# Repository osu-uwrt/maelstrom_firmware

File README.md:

# maelstrom_firmware

This repository holds the code for the embedded systems and other tools running on Maelstrom. There are two primary parts to this: the acoustics code, and the the coprocessor code/console. A brief overview of each of the systems is below. For detailed install instructions, see the acoustics and [copro](/Copro/README.md) README files. For more information about the hardware of these devices, see github.com/osu-uwrt/uwrt_electronics

## Coprocessor
The coprocessor has several primary tasks:

- read sensor values
- control thrusters
- communicate with the main computer

It does this with an onboard microcontroller, an STM32F405RGT6. This microcontroller board is loosely based on the pyboard from the micropython project. As such, the microcontroller is programmed using micropython. It is programmed using a USB connection, and talks with the main computer over the local network via websocket. Additionally, there is an operator console web app that shows current status of the coprocessor and allows the device to be controlled without having to open up the vehicle.

## Acoustics
The acoustics system is designed to be able to determine the direction and distance of an acoustic ping (between 20kHz - 40kHz frequency). This is used to navigate towards a pinger in the robot. Thus, the device has a lot of signal processing and alignment code

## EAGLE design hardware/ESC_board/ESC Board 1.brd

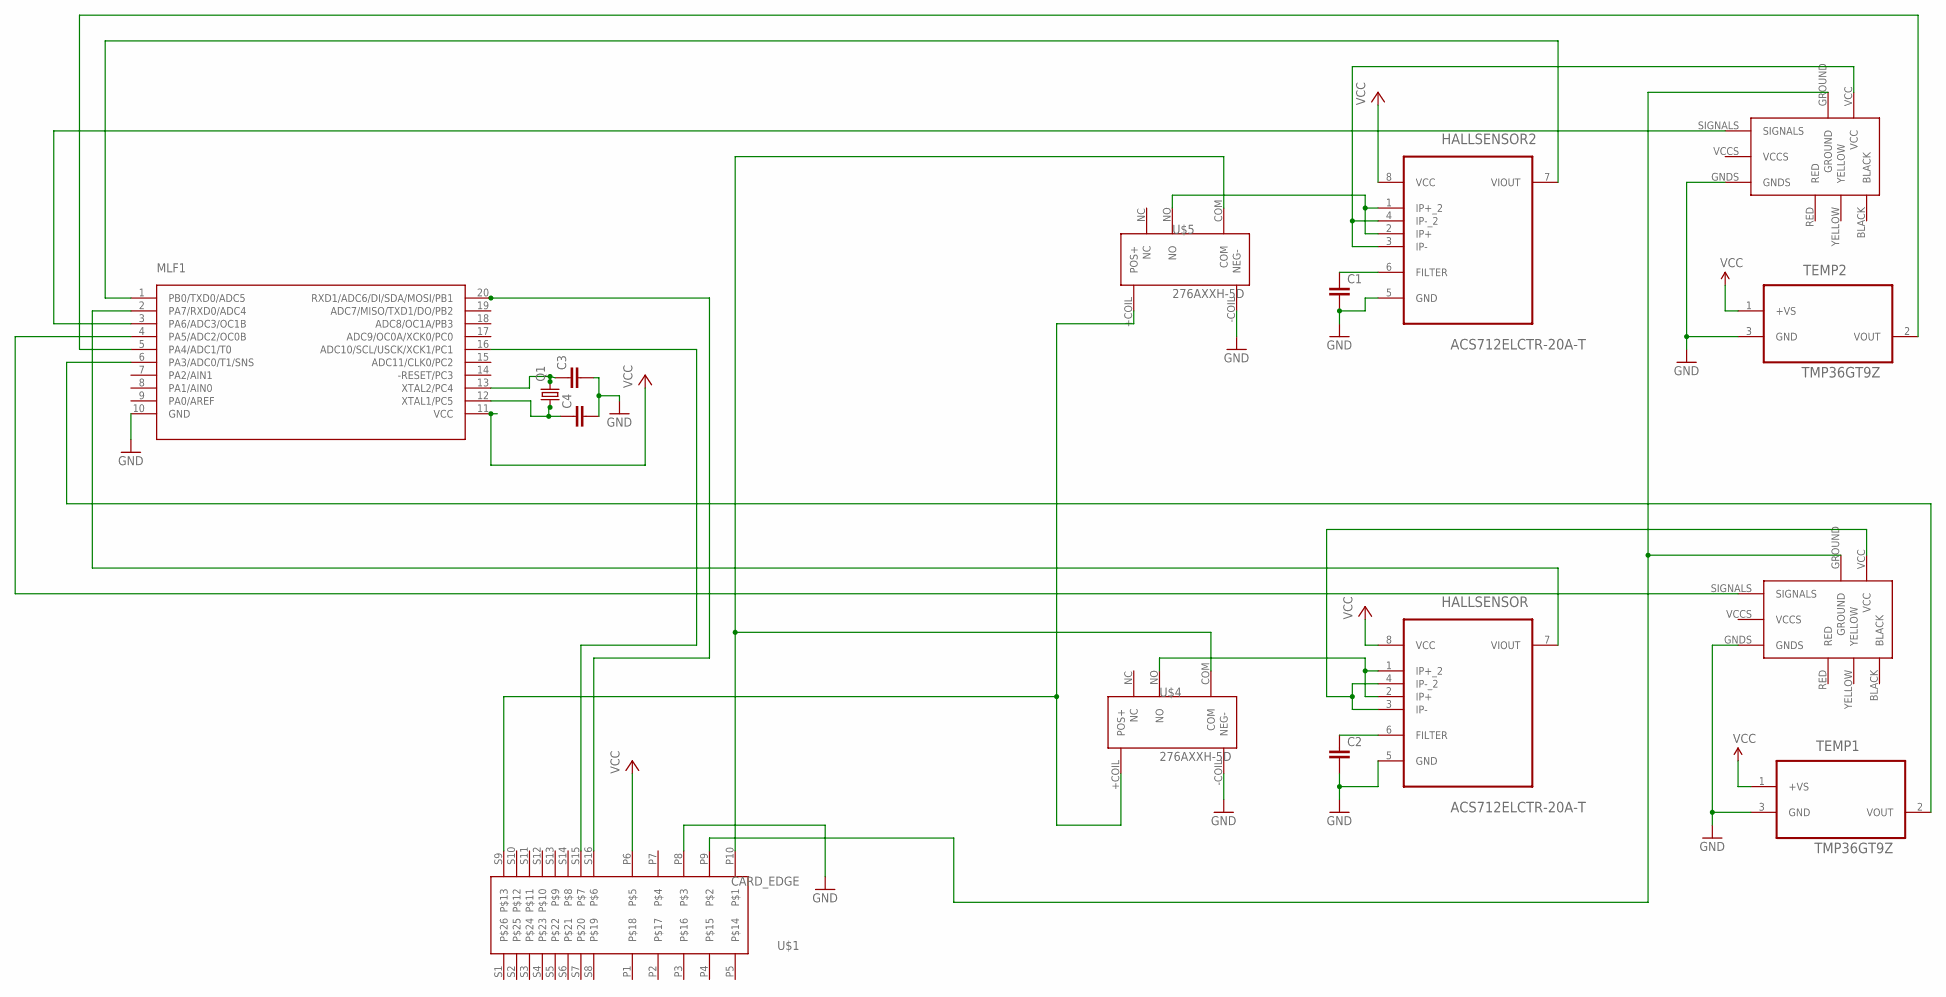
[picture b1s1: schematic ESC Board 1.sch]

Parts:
C1, C2, C3, C4: CAPEZ; CAP-PTH-SMALLEZ
HALLSENSOR, HALLSENSOR2: ACS712ELCTR-20A-T; SOIC127P600X175-8N
MLF1: ATTINY1634SOIC20; SOIC20
Q1: CRYTALTC26V; TC26V
TEMP1, TEMP2: TMP36GT9Z; TO127P254X533-3P
U$1: CARD_EDGE; EDGE_CONNECTOR
U$2, U$3: ESC30A; 30AESC
U$4, U$5: 276AXXH-5D

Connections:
BAT-: U$1.P9, U$2.GROUND, U$3.GROUND
GND: C1.2, C2.2, C3.2, C4.2, HALLSENSOR.5 (GND), HALLSENSOR2.5 (GND), MLF1.10 (GND), TEMP1.3 (GND), TEMP2.3 (GND), U$1.P8, U$2.GNDS, U$3.GNDS, U$4.-COIL (NEG-), U$5.-COIL (NEG-)
unnamed: MLF1.5 (PA4/ADC1/T0), TEMP2.2 (VOUT)
unnamed: MLF1.6 (PA3/ADC0/T1/SNS), TEMP1.2 (VOUT)
unnamed: MLF1.20 (RXD1/ADC6/DI/SDA/MOSI/PB1), U$1.S16
unnamed: MLF1.16 (ADC10/SCL/USCK/XCK1/PC1), U$1.S15
unnamed: HALLSENSOR2.7 (VIOUT), MLF1.1 (PB0/TXD0/ADC5)
unnamed: HALLSENSOR.7 (VIOUT), MLF1.2 (PA7/RXD0/ADC4)
unnamed: C3.1, MLF1.13 (XTAL2/PC4), Q1.2
unnamed: C4.1, MLF1.12 (XTAL1/PC5), Q1.1
unnamed: C1.1, HALLSENSOR2.6 (FILTER)
unnamed: HALLSENSOR2.3 (IP-), HALLSENSOR2.4 (IP-_2), U$3.VCC
unnamed: U$1.P10, U$4.COM, U$5.COM
unnamed: HALLSENSOR.3 (IP-), HALLSENSOR.4 (IP-_2), U$2.VCC
unnamed: MLF1.4 (PA5/ADC2/OC0B), U$2.SIGNALS
unnamed: MLF1.3 (PA6/ADC3/OC1B), U$3.SIGNALS
unnamed: C2.1, HALLSENSOR.6 (FILTER)
unnamed: HALLSENSOR.1 (IP+_2), HALLSENSOR.2 (IP+), U$4.NO
unnamed: HALLSENSOR2.1 (IP+_2), HALLSENSOR2.2 (IP+), U$5.NO
unnamed: U$1.S9, U$4.+COIL (POS+), U$5.+COIL (POS+)
VCC: HALLSENSOR.8 (VCC), HALLSENSOR2.8 (VCC), MLF1.11 (VCC), TEMP1.1 (+VS), TEMP2.1 (+VS), U$1.P6

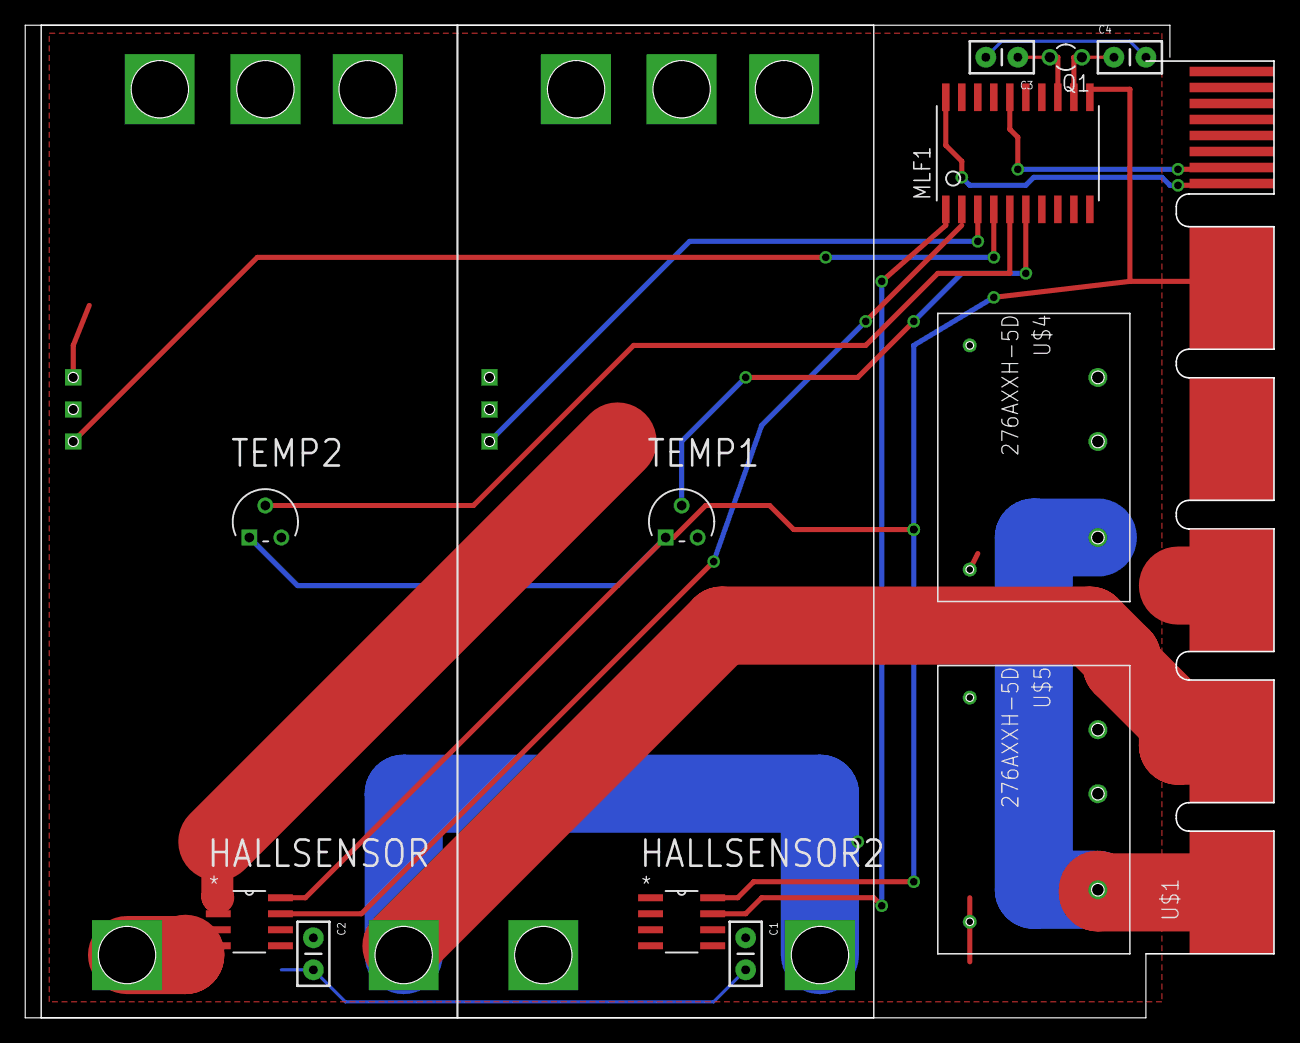
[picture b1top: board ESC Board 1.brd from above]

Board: 2 copper layers, 99.0 x 78.6 mm, 15 parts (0 on the bottom side), 21 nets.

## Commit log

2016-06-17 Move serial to hardware.
2016-06-17 Rename ATmega source files.
2016-06-17 Rewrite thruster controller.
2016-06-18 Add TWI library for ESC microcontrollers.
2016-06-18 Add ESC board firmware.
2016-06-18 Correct thruster controller firmware.
2016-06-20 Bit shift TWI data.
2016-06-22 Monitor power distribution board.
2016-06-26 Monitor battery output.
2016-06-29 It's giving me... attitude.
2016-06-30 internal oscillator calibration values, offset initial clock values
2016-06-30 rebased with iconor/master
2016-06-30 Update firmware timing and calibrate current sensors.
2016-07-01 Update power monitor rate.
2016-07-02 depth sensor
2016-07-02 Succesfully reads depth.
2016-07-02 Repair thruster controller sketch.
2016-09-07 added eagle files
2016-09-18 added up to date firmware
2016-10-24 total redesign is way better
2016-10-24 Update directory/file names.
2017-08-10 Putting old stuff into /old
2017-08-10 Initial commit of the firmware for the Co-Pro board
2017-08-11 Adding in coPro and powerSupply boards, might be moved later
2017-09-06 Cleaning up Hardware and Firmware, function prototype for LED
2017-09-06 Attempting to use the HAL API to handle all of our pin needs
2017-09-06 Adding Arduino Code and splitting to STM32 code
2017-09-07 Adding initial depth sensor firmware waiting for Benji to confirm
2017-09-08 Testing HAL initialization of stuff along with dabbling in ideas to split the team code out of the src
2017-09-08 Adding the README file
2017-09-10 Adding Team threads for Arduino replacement
2017-09-11 Adding Arduino/C based ros_lib to STM32
2017-09-11 Updated the Makefile to build
2017-10-06 Changed pins on arduino code for 10/7 pool test
2017-10-07 This should fix it, but who knows
2017-11-12 Initial commit of the rev 1 copro pin map
2018-01-25 Working commit of sanity
2018-02-12 Ordinary cleanup of our sins
2018-02-12 Initial commit of a Bibyk Abstraction layer by altering STM code less
2018-02-12 Adding stmComms, test suite with riptideSTM and computer communications
2018-02-12 Removed .idea and .DS_Store files, added .gitignore
2018-02-15 added queue example code
2018-02-15 add serial template for f405 (using FS)
2018-02-18 added new project, need to test
2018-02-18 Updating gitignore to ignore build files and cmake stuffs
2018-02-18 Updating the riptideSTM, abstraction works theoretically
2018-02-18 Yikes git is hard
2018-02-18 fixed the bugs
2018-02-19 Updating the switch messages for the copro rev1
2018-03-01 initial project commit
2018-03-01 working serial code for pool test - old board
2018-03-01 check message length implemented
2018-03-01 finished kill switch
2018-03-02 i2c is working, still need to format the message
2018-03-03 code complete; need to test
2018-03-04 revisions from pool test
2018-03-22 Just for Gus
2018-03-23 working with copro v3
2018-03-23 Revert "Merge branch 'march_pool_test' into new_changes"
    This reverts commit bc184a939472e353ee53c2bbd46ac80ecc62abe6, reversing
    changes made to 817e7272e0bf183608458219f8eef7cdb89f3fc0.
2018-03-23 Revert "working with copro v3"
    This reverts commit 817e7272e0bf183608458219f8eef7cdb89f3fc0.
2018-03-23 add folder and ioc - base start point
2018-03-23 Restored to working v3
2018-03-23 good depth sensor, need to test
2018-03-23 refactored ioc and cleaned up a bit
2018-03-25 Cleanup attempt 1
2018-03-25 Cleanup attempt 2
2018-03-25 Cleanup attempt
2018-03-25 working pool test code + unfinished i2c
2018-04-13 working april pool test - fixed depth sensor ftostring function
2018-05-16 Deleting old stuff out of repo
2018-05-16 Initial commit of mirkwood
2018-05-16 Updating Makefile to compile
2018-05-16 Going back to our roots, working but no status board
2018-05-16 Cleanup of old RTOS stuffs
2018-05-16 Migrating back to Atom building now
2018-05-16 Actually starting everything working temp
2018-05-16 Fixing print to display, temperature accurate
2018-05-16 Starting PWM timers, this is important
2018-05-17 Adding call for hardfault handler, working 517
2018-05-18 Adding current calculations for the battery balancer
2018-05-22 Fixing header file names
2018-05-28 Updating the .gitirnore
2018-05-28 Tyring to ignore the build files
2018-05-28 Adding the startup function to status board
2018-05-28 Global thermonuclear war of master
2018-05-28 Cleaning up the mirkwood branch
2018-05-28 Readme now reflects what we know
2018-05-31 Added acoustics
2018-06-06 Adding electro status message
2018-06-06 Merging the mirkwood branch with master
2018-06-22 latest FPGA
2018-06-22 Update gitignore
2018-06-27 Updating README and STM32 folder to reflect current code
2018-06-27 Adding the pneumatics arduino code
2018-06-27 Changing vehicle name
2018-09-21 New acoustics configuration with ddr3
2018-10-29 Commenting acoustics code
2018-10-29 Fixing errors
2018-11-16 Trying to fix broken fpga
2018-11-18 Fixed acoustics. Works with new board
2019-02-18 Addition of new copro stuff
2019-02-18 Updating gitignore
2019-02-18 Gitignore fix
2019-02-18 Python 3 compatibility
2019-02-18 More compatible
2019-02-19 Works on python 3
2019-02-20 Python 2 compatibility
2019-02-21 Adding polling example and allowing multiple commands to come through at once
2019-02-21 Comments
2019-02-21 python 2/3 support
2019-03-16 Adding hal
2019-03-16 website changes
2019-03-17 Updating httpproxy for copro
2019-03-17 Making the code work
2019-03-17 Implementing thruster off and temp
2019-03-17 Cleaning out website
2019-03-17 Fixing vulnerabilities
2019-03-18 Implementing temp and power graph plus copro code
2019-03-19 Error handling, leds, and pwm
2019-03-19 Added depth code
2019-03-20 Now able to get current state of copro
2019-03-21 Fixing control lines and adding status light code
2019-03-21 Fixed electricity plot and added switches command
2019-03-22 Depth works
2019-03-22 Quick fix
2019-03-23 Making it run on pc
2019-03-24 Cleaning up repo
2019-03-25 current stuff
2019-03-25 Cleanup and branding
2019-03-26 Fixed some issues with copro
2019-03-27 Works on all python 3
2019-03-27 depth card component
2019-03-27 Small changes
2019-04-02 enable closing of sockets
2019-04-02 Forgot to commit this
2019-04-21 added/fixed thruster current collection
2019-04-21 create command tester tool and update hal simulator
2019-04-21 Update main README
2019-04-21 Create copro docs
2019-04-21 add copro config files
2019-04-27 changed mobopower and thrusterpower to 12V and 5V
2019-04-27 New depth
2019-04-29 Better simulator
2019-05-01 Fixing some issues
2019-05-17 Added reset button and fixed copro bugs
2019-05-30 Reset switch
2019-06-06 Killswitch time and readme update
2019-06-06 Fixing depth sensor
2019-06-06 Ensure that time will work even on the wrap over
2019-06-08 Improved comms
2019-06-08 Fixing memory
2019-06-08 5V reset functionality on copro
2019-06-08 5V reset on copro
2019-06-11 Updating httpProxy
2019-07-15 thruster default on
2019-07-16 Thusters default on, after batteries are plugged in they will wait for one to dip below 18.5V and then disable the thrusters
2019-07-20 Initial commit of actuator firmware (arduino)
2019-07-24 Debugging
2019-07-24 Adding actuator board functionality
2019-07-24 Basics of actuator communication
2019-07-26 Last changes
2019-09-15 memory leak fix
2019-09-15 Fixed halSimulated and fixed memory fix
2019-09-15 fixed hal simulated
2019-09-19 Updated simulator and command tester
2019-09-22 Fix the variable unsable warning
2019-09-22 Added error checking to each thread
2019-09-22 I create a auto cooling funciton.
2019-10-12 I add function to see memory usage
2019-10-12 Just make it look neatly
2019-10-13 Command tester fix
2019-10-13 FIx some bugs and make sure everything is fine
2019-10-13 Fix memory monitor bug, add temp control funciton
2019-10-13 Added memory to operator console
2019-10-13 Remove TODO and modify the parameter of battery
2019-10-13 Added latency and thermostate to operator console
2020-01-30 Bump tinymce from 4.5.7 to 4.9.7 in /Copro/operator_console/website
    Bumps [tinymce](https://github.com/tinymce/tinymce-dist) from 4.5.7 to 4.9.7.
    - [Release notes](https://github.com/tinymce/tinymce-dist/releases)
    - [Changelog](https://github.com/tinymce/tinymce-dist/blob/4.9.7/changelog.txt)
    - [Commits](https://github.com/tinymce/tinymce-dist/compare/4.5.7...4.9.7)
2020-05-11 Bump tinymce from 4.5.7 to 4.9.10 in /Copro/operator_console/website
    Bumps [tinymce](https://github.com/tinymce/tinymce-dist) from 4.5.7 to 4.9.10.
    - [Release notes](https://github.com/tinymce/tinymce-dist/releases)
    - [Changelog](https://github.com/tinymce/tinymce-dist/blob/4.9.10/changelog.txt)
    - [Commits](https://github.com/tinymce/tinymce-dist/compare/4.5.7...4.9.10)
2020-08-11 Bump tinymce from 4.5.7 to 4.9.11 in /Copro/operator_console/website
    Bumps [tinymce](https://github.com/tinymce/tinymce-dist) from 4.5.7 to 4.9.11.
    - [Release notes](https://github.com/tinymce/tinymce-dist/releases)
    - [Changelog](https://github.com/tinymce/tinymce-dist/blob/4.9.11/changelog.txt)
    - [Commits](https://github.com/tinymce/tinymce-dist/compare/4.5.7...4.9.11)
2021-01-06 Bump tinymce from 4.5.7 to 5.6.0 in /Copro/operator_console/website
    Bumps [tinymce](https://github.com/tinymce/tinymce-dist) from 4.5.7 to 5.6.0.
    - [Release notes](https://github.com/tinymce/tinymce-dist/releases)
    - [Changelog](https://github.com/tinymce/tinymce-dist/blob/master/changelog.txt)
    - [Commits](https://github.com/tinymce/tinymce-dist/compare/4.5.7...5.6.0)
2021-02-20 Implemented new commands added in titan
2021-02-22 Improved fault handling
2021-02-22 Added watchdog support
2021-02-22 Added watchdog logging
2021-02-22 Watchdog bug fix
2021-02-23 Added hello message and increased watchdog timeout
2021-02-23 Added client hello
2021-02-28 Added connection timeouts
2021-03-05 Disable converter board ADC init
2021-03-14 Fix bug with thruster current greater than 255
2021-04-25 Fixed Bugs

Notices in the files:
parts and their libraries:
SparkFun-Capacitors: Licensing: Creative Commons ShareAlike 4.0 International - https://creativecommons.org/licenses/by-sa/4.0
